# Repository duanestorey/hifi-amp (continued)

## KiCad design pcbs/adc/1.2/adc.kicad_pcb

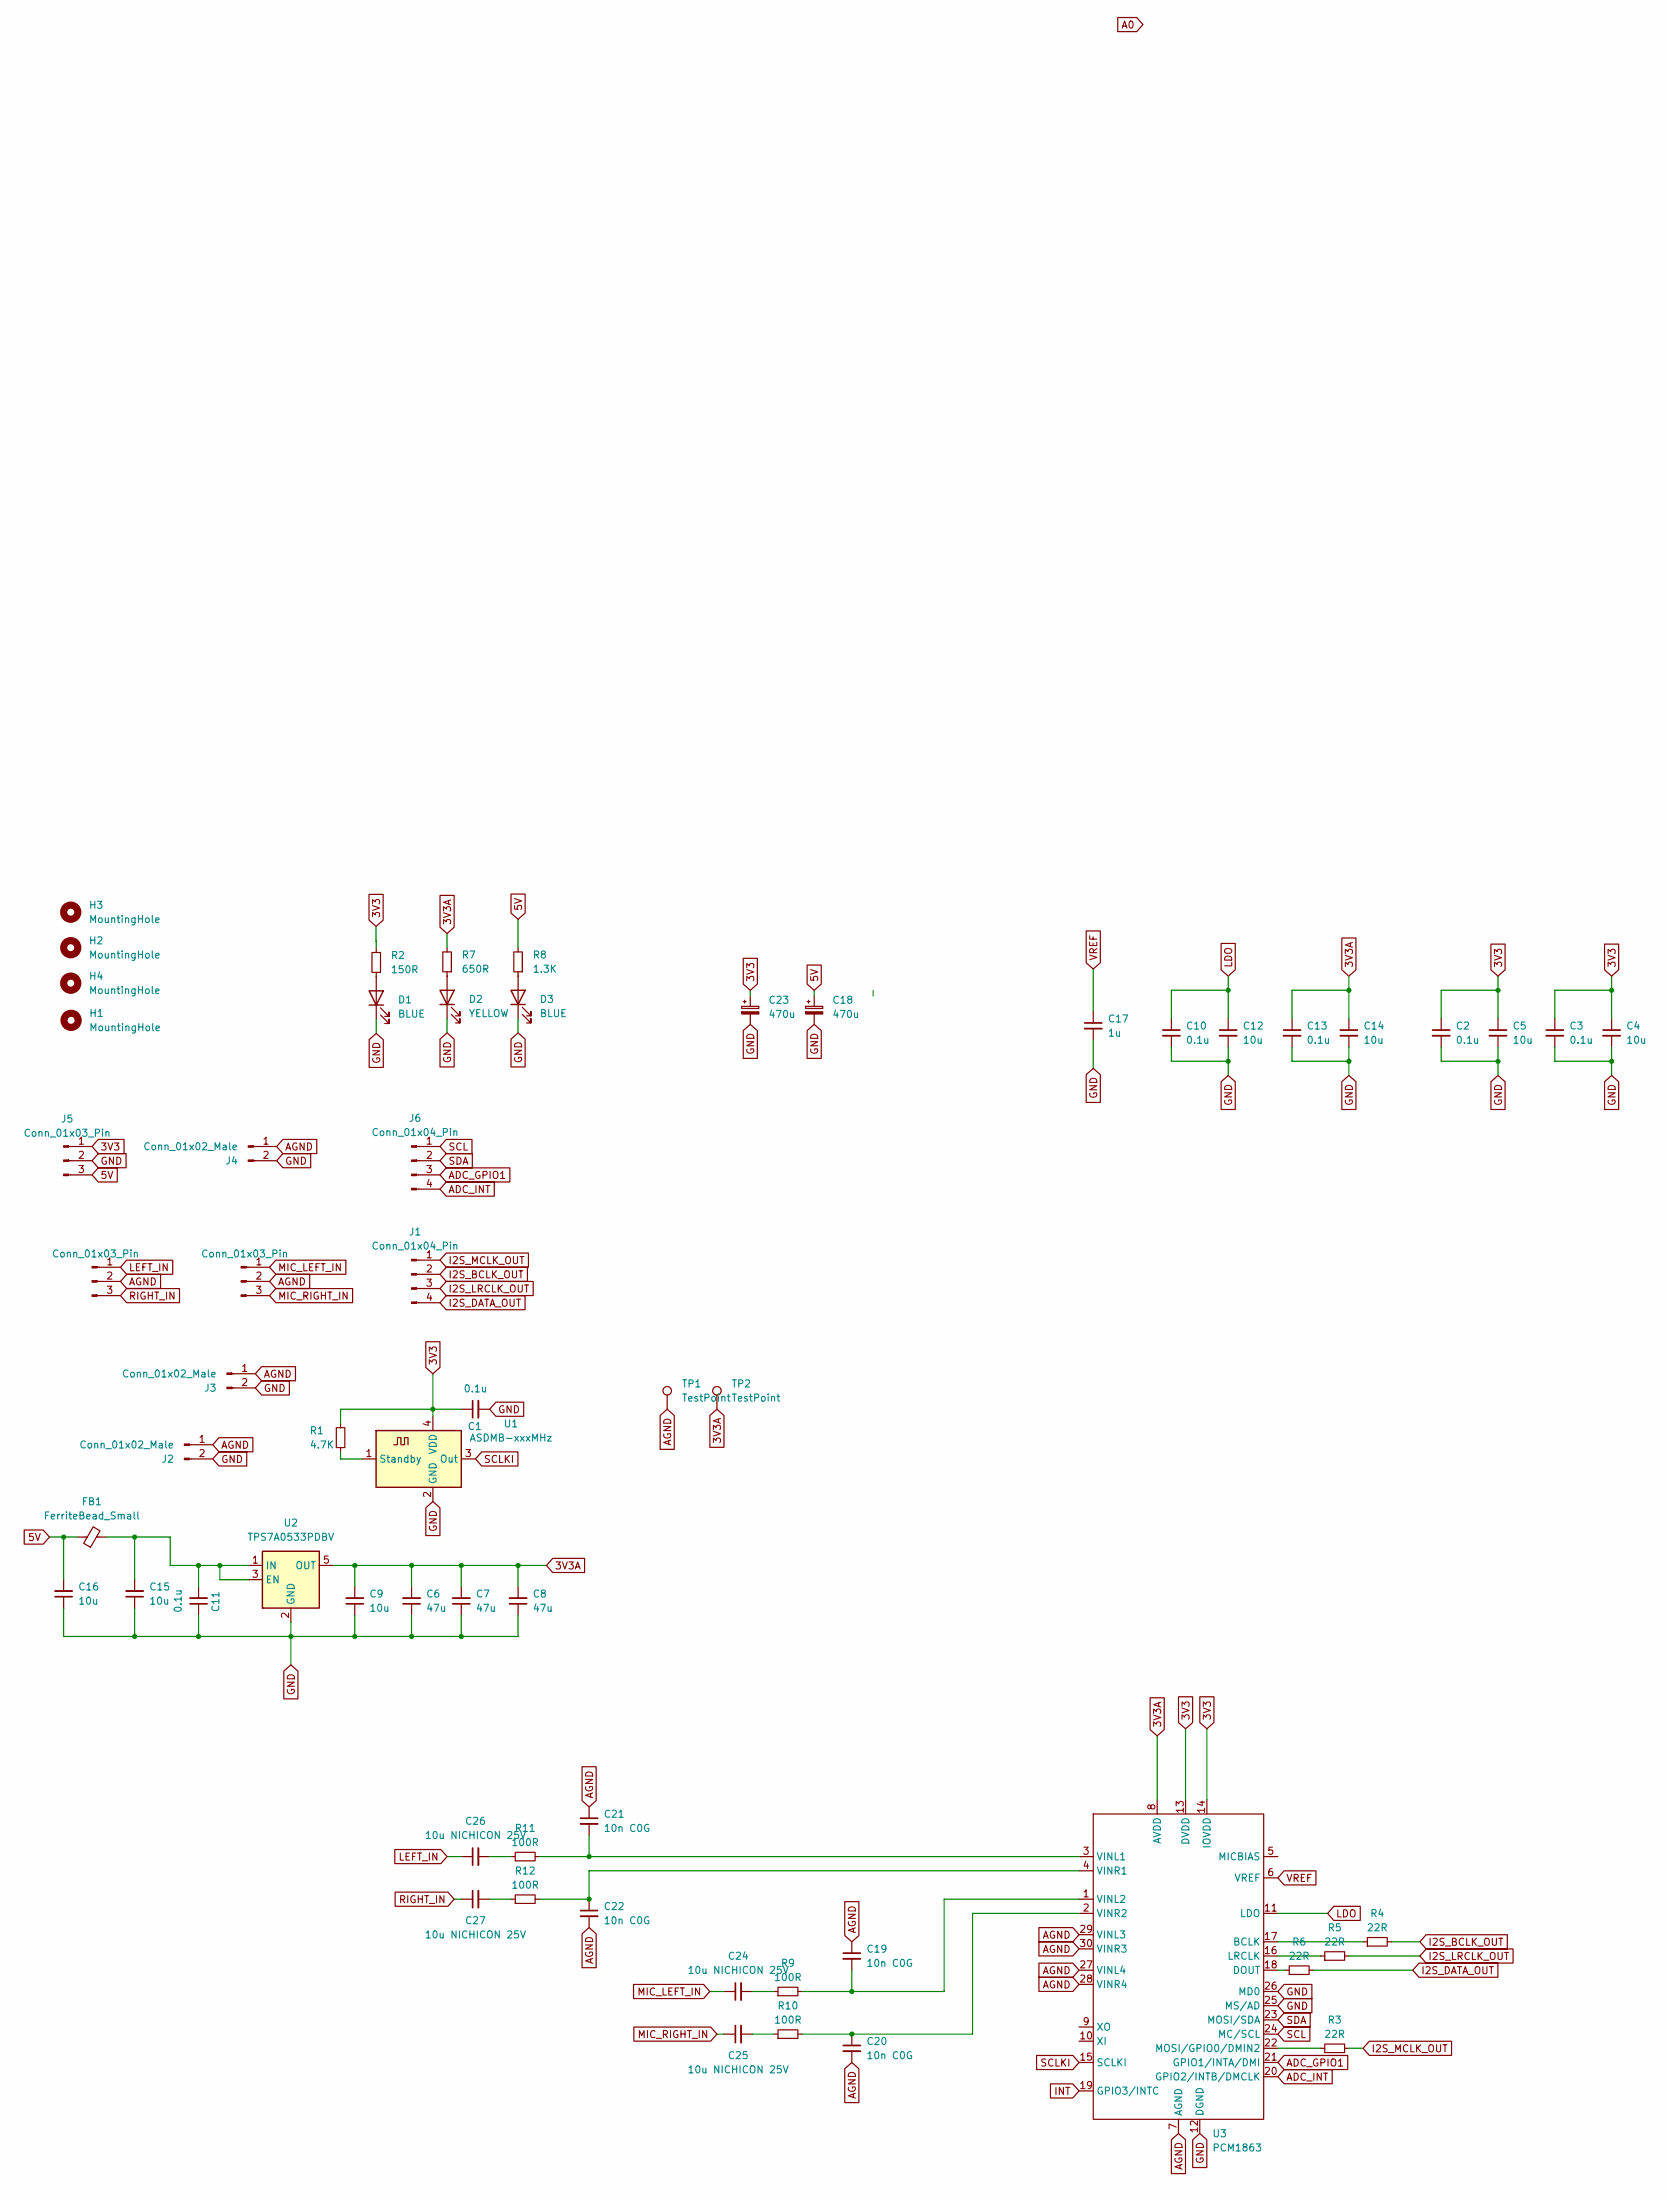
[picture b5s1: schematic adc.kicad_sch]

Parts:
C1, C11: 0.1u; C_0805_2012Metric_Pad1.18x1.45mm_HandSolder; Mouser 791-0805N103G250CT
C2, C3, C10, C13: 0.1u; C_0805_2012Metric_Pad1.18x1.45mm_HandSolder
C4, C5, C9, C12, C14, C15, C16: 10u; C_1206_3216Metric_Pad1.33x1.80mm_HandSolder
C6, C7, C8: 47u; C_1206_3216Metric_Pad1.33x1.80mm_HandSolder
C17: 1u; C_1206_3216Metric_Pad1.33x1.80mm_HandSolder
C18, C23: 470u; CP_Radial_D6.3mm_P2.50mm
C19, C20, C21, C22: 10n C0G; C_0805_2012Metric_Pad1.18x1.45mm_HandSolder; Mouser 791-0805N103G250CT
C24, C25, C26, C27: 10u NICHICON 25V; CP_Radial_D5.0mm_P2.00mm
D1, D3: BLUE; LED_0603_1608Metric
D2: YELLOW; LED_0603_1608Metric
FB1: FerriteBead_Small; R_0603_1608Metric_Pad0.98x0.95mm_HandSolder
H1, H2, H3, H4: MountingHole; MountingHole_3.2mm_M3_DIN965_Pad_TopOnly
J1, J6: Conn_01x04_Pin; JST_PH_B4B-PH-K_1x04_P2.00mm_Vertical
J2, J3, J4: Conn_01x02_Male; PinHeader_1x02_P2.54mm_Vertical
J5, J7, J8: Conn_01x03_Pin; JST_PH_B3B-PH-K_1x03_P2.00mm_Vertical
R1: 4.7K; R_0603_1608Metric_Pad0.98x0.95mm_HandSolder; Mouser 603-RT0805FRE0722RL
R2: 150R; R_0603_1608Metric_Pad0.98x0.95mm_HandSolder
R3, R4, R5, R6: 22R; R_0805_2012Metric_Pad1.20x1.40mm_HandSolder; Mouser 603-RT0805FRE0722RL
R7: 650R; R_0603_1608Metric_Pad0.98x0.95mm_HandSolder
R8: 1.3K; R_0603_1608Metric_Pad0.98x0.95mm_HandSolder
R9, R10, R11, R12: 100R; R_0805_2012Metric_Pad1.20x1.40mm_HandSolder; Mouser 603-RT0805FRE13100RL
TP1, TP2: TestPoint; TestPoint_THTPad_2.5x2.5mm_Drill1.2mm
U1: ASDMB-xxxMHz; Oscillator_SMD_Abracon_ASE-4Pin_3.2x2.5mm; Mouser 346-3225Z24.5760C1KX
U2: TPS7A0533PDBV; SOT-23-5
U3: PCM1863; TSSOP-30_4.4x7.8mm_P0.5mm; Mouser 595-PCM1863DBT

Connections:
3V3: C1.1, C2.1, C3.1, C4.1, C5.1, C23.1, J5.1, R1.1, R2.2, U1.4 (VDD), U3.13 (DVDD), U3.14 (IOVDD)
3V3A: C6.2, C7.2, C8.2, C9.2, C13.1, C14.1, R7.2, TP2.1, U2.5 (OUT), U3.8 (AVDD)
5V: C16.2, C18.1, FB1.1, J5.3, R8.2
ADC_GPIO1: J6.3, U3.21 (GPIO1/INTA/DMI)
ADC_INT: J6.4, U3.20 (GPIO2/INTB/DMCLK)
AGND: C19.1, C20.2, C21.1, C22.2, J2.1, J3.1, J4.1, J7.2, J8.2, TP1.1, U3.7 (AGND), U3.27 (VINL4), U3.28 (VINR4), U3.29 (VINL3), U3.30 (VINR3)
GND: C1.2, C2.2, C3.2, C4.2, C5.2, C6.1, C7.1, C8.1, C9.1, C10.2, C11.1, C12.2, C13.2, C14.2, C15.1, C16.1, C17.2, C18.2, C23.2, D1.1 (K), D2.1 (K), D3.1 (K), J2.2, J3.2, J4.2, J5.2, U1.2 (GND), U2.2 (GND), U3.12 (DGND), U3.25 (MS/AD), U3.26 (MD0)
I2S_BCLK_OUT: J1.2, R4.2
I2S_DATA_OUT: J1.4, R6.2
I2S_LRCLK_OUT: J1.3, R5.2
I2S_MCLK_OUT: J1.1, R3.2
INT: U3.19 (GPIO3/INTC)
LDO: C10.1, C12.1, U3.11 (LDO)
LEFT_IN: C26.1, J8.1
MIC_LEFT_IN: C24.1, J7.1
MIC_RIGHT_IN: C25.1, J7.3
unnamed: C24.2, R9.1
unnamed: C25.2, R10.1
unnamed: C26.2, R11.1
unnamed: C27.2, R12.1
unnamed: D1.2 (A), R2.1
unnamed: D2.2 (A), R7.1
unnamed: D3.2 (A), R8.1
unnamed: R1.2, U1.1 (Standby)
unnamed: C11.2, C15.2, FB1.2, U2.1 (IN), U2.3 (EN)
unnamed: R4.1, U3.17 (BCLK)
unnamed: R6.1, U3.18 (DOUT)
unnamed: R5.1, U3.16 (LRCLK)
unnamed: R3.1, U3.22 (MOSI/GPIO0/DMIN2)
unnamed: C21.2, R11.2, U3.3 (VINL1)
unnamed: C19.2, R9.2, U3.1 (VINL2)
unnamed: C22.1, R12.2, U3.4 (VINR1)
unnamed: C20.1, R10.2, U3.2 (VINR2)
RIGHT_IN: C27.1, J8.3
SCL: J6.1, U3.24 (MC/SCL)
SCLKI: U1.3 (Out), U3.15 (SCLKI)
SDA: J6.2, U3.23 (MOSI/SDA)
VREF: C17.1, U3.6 (VREF)

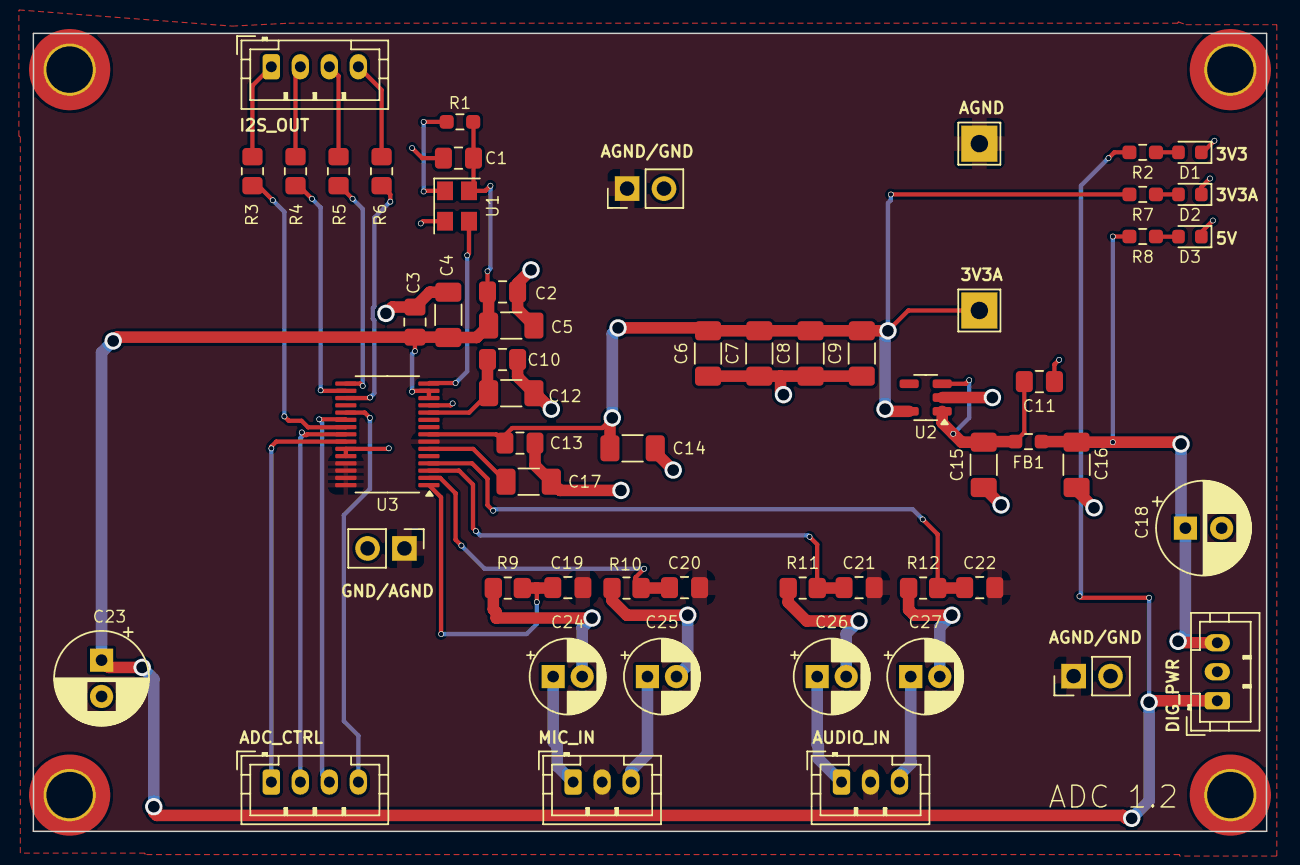
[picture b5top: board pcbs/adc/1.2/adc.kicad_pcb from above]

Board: 2 copper layers, 85.0 x 55.0 mm, 60 parts (0 on the bottom side), 37 nets.

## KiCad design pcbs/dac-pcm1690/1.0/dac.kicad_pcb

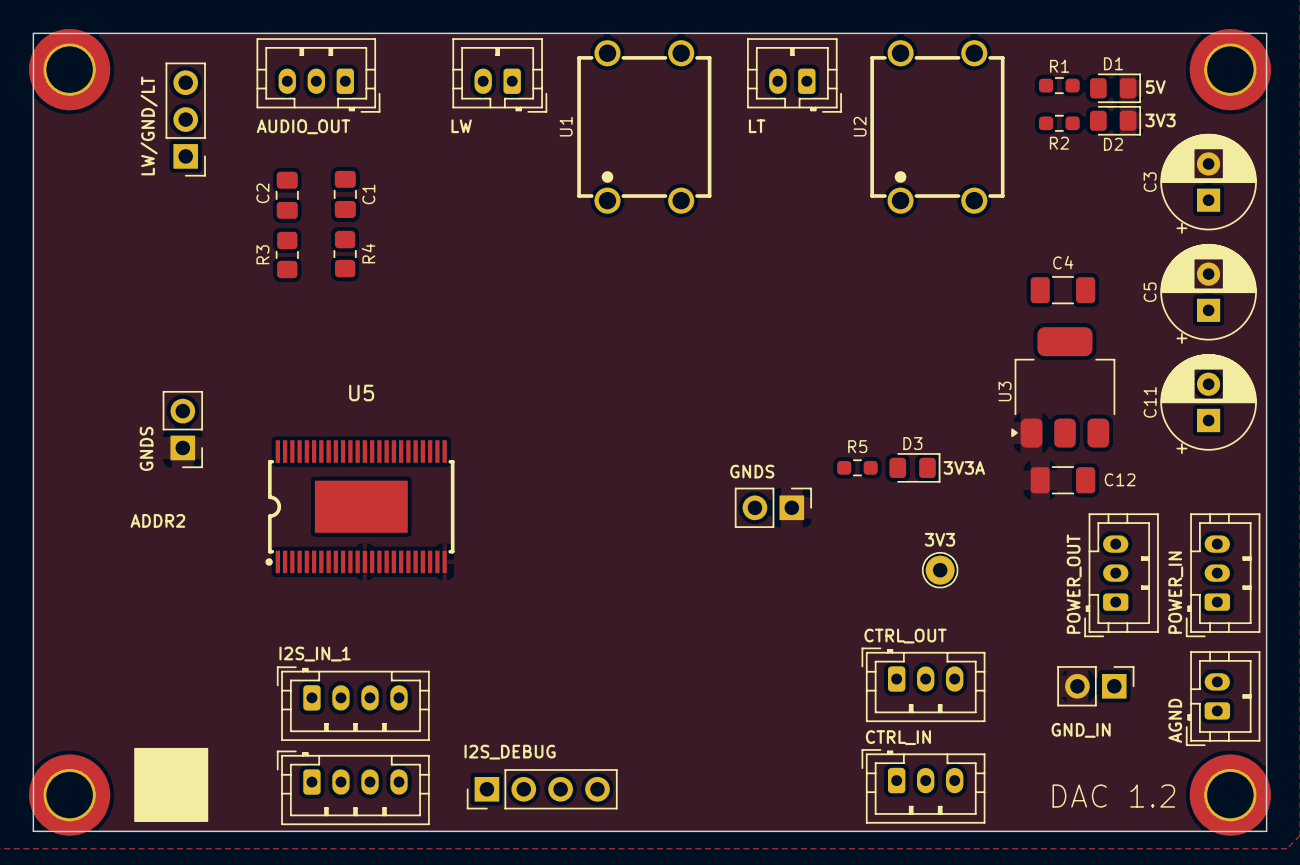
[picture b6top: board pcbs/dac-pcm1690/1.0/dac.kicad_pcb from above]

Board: 2 copper layers, 85.0 x 55.0 mm, 39 parts (0 on the bottom side), 22 nets, no tracks yet.

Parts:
C1, C2: 2.2n 50V C0G; C_0805_2012Metric_Pad1.18x1.45mm_HandSolder
C3, C5, C11: 220u; CP_Radial_D6.3mm_P2.50mm
C4, C12: 10U; C_1206_3216Metric_Pad1.33x1.80mm_HandSolder
D1: RED; LED_0805_2012Metric_Pad1.15x1.40mm_HandSolder
D2, D3: BLUE; LED_0805_2012Metric_Pad1.15x1.40mm_HandSolder
H1, H2, H3, H4: MountingHole; MountingHole_3.2mm_M3_DIN965_Pad_TopOnly
J1, J7, J13, J15, J16: Conn_01x03_Pin; JST_PH_B3B-PH-K_1x03_P2.00mm_Vertical
J2, J3, J18: Conn_01x02_Pin; JST_PH_B2B-PH-K_1x02_P2.00mm_Vertical
J4: Conn_01x03_Pin; PinHeader_1x03_P2.54mm_Vertical
J5, J10, J11: Conn_01x02_Pin; PinHeader_1x02_P2.54mm_Vertical
J12, J14: Conn_01x04_Pin; JST_PH_B4B-PH-K_1x04_P2.00mm_Vertical
J17: Conn_01x04_Pin; PinHeader_1x04_P2.54mm_Vertical
R1: 1.3K; R_0603_1608Metric_Pad0.98x0.95mm_HandSolder
R2, R5: 150R; R_0603_1608Metric_Pad0.98x0.95mm_HandSolder
R3, R4: 470R TF; R_0805_2012Metric_Pad1.20x1.40mm_HandSolder
TP4: TestPoint; TestPoint_THTPad_D2.0mm_Drill1.0mm
U1, U2: DA101C_C6931652; XFMR-TH_4P-L9.5-W9.0-P5.08-LS10.2_C9900096976
U3: ZLDO1117QG33TA; SOT-223-3_TabPin2
U5: PCM1690DCAR; HTSSOP-48_L12.5-W6.1-P0.50-LS8.1-BL-EP-1

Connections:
3V3: C3.1, J7.1, J13.1, R2.1, TP4.1, U5.12 (VDD)
3V3A: C4.1, C11.1, R5.1, U3.2 (VO)
5V: C5.1, C12.1, J7.3, J13.3, R1.1, U3.3 (VI), U5.25 (VCC1), U5.47 (VCC2)
AGND: C1.1, C2.1, C4.2, C11.2, D3.1 (K), J1.2, J4.2, J5.2, J10.2, J18.1, J18.2, U1.3, U2.3, U5.1 (RSV2), U5.3 (RSV2), U5.5 (RSV2), U5.27 (AGND1), U5.28 (RSV2), U5.46 (AGND2)
BCLK: J12.2, J14.2, J17.2
DATA: J12.4, J14.4, J17.4
GND: C3.2, C5.2, C12.2, D1.1 (K), D2.1 (K), J5.1, J10.1, J11.2, U3.1 (GND), U5.13 (DGND), U5.24 (MODE)
GND_IN: J7.2, J11.1, J13.2
LEFT_TWEETER: C2.2, J1.3, J4.3, R3.2, U2.1
LEFT_WOOFER: C1.2, J1.1, J4.1, R4.2, U1.1
LRCLK: J12.3, J14.3, J17.3
unnamed: D1.2 (A), R1.2
unnamed: D2.2 (A), R2.2
unnamed: D3.2 (A), R5.2
SCL: J15.1, J16.1
SCLK: J12.1, J14.1, J17.1
SDA: J15.2, J16.2
SWL_NEG: J2.1, U1.4
SWL_OUT: J2.2, U1.6
SWR_NEG: J3.1, U2.4
SWR_OUT: J3.2, U2.6
XSMT_IN: J15.3, J16.3

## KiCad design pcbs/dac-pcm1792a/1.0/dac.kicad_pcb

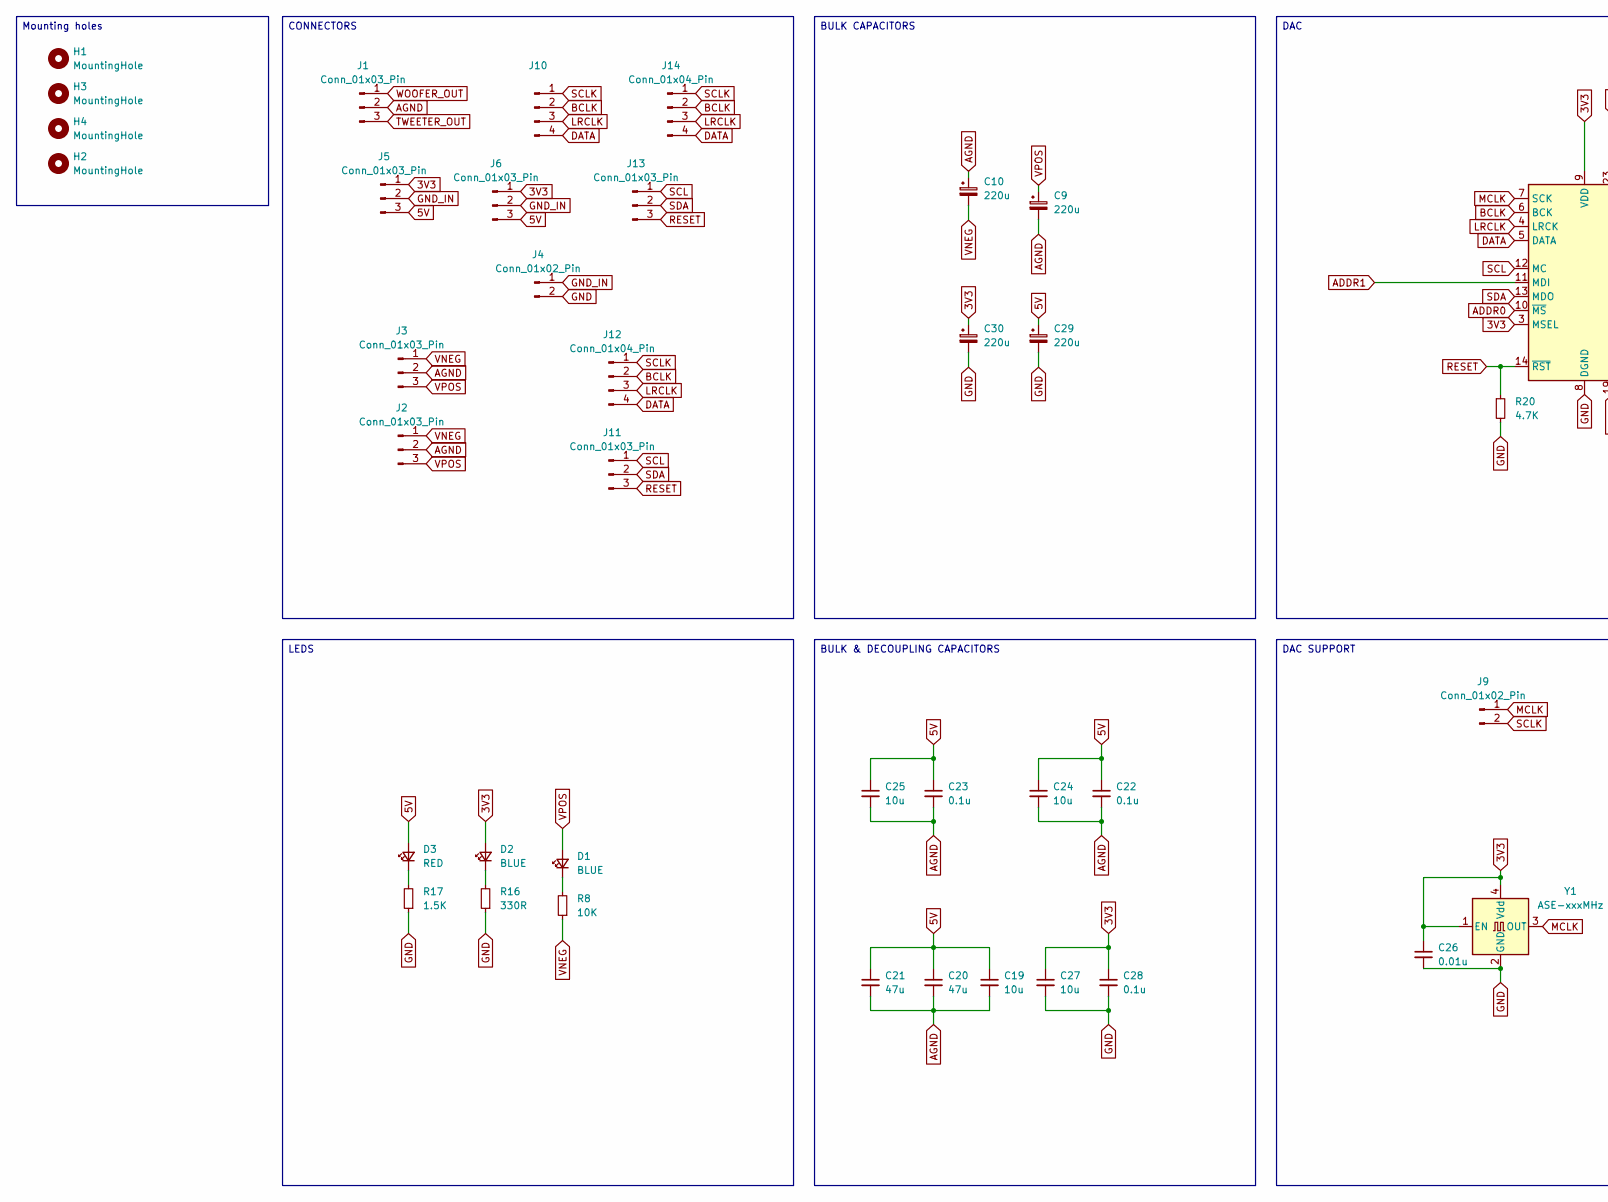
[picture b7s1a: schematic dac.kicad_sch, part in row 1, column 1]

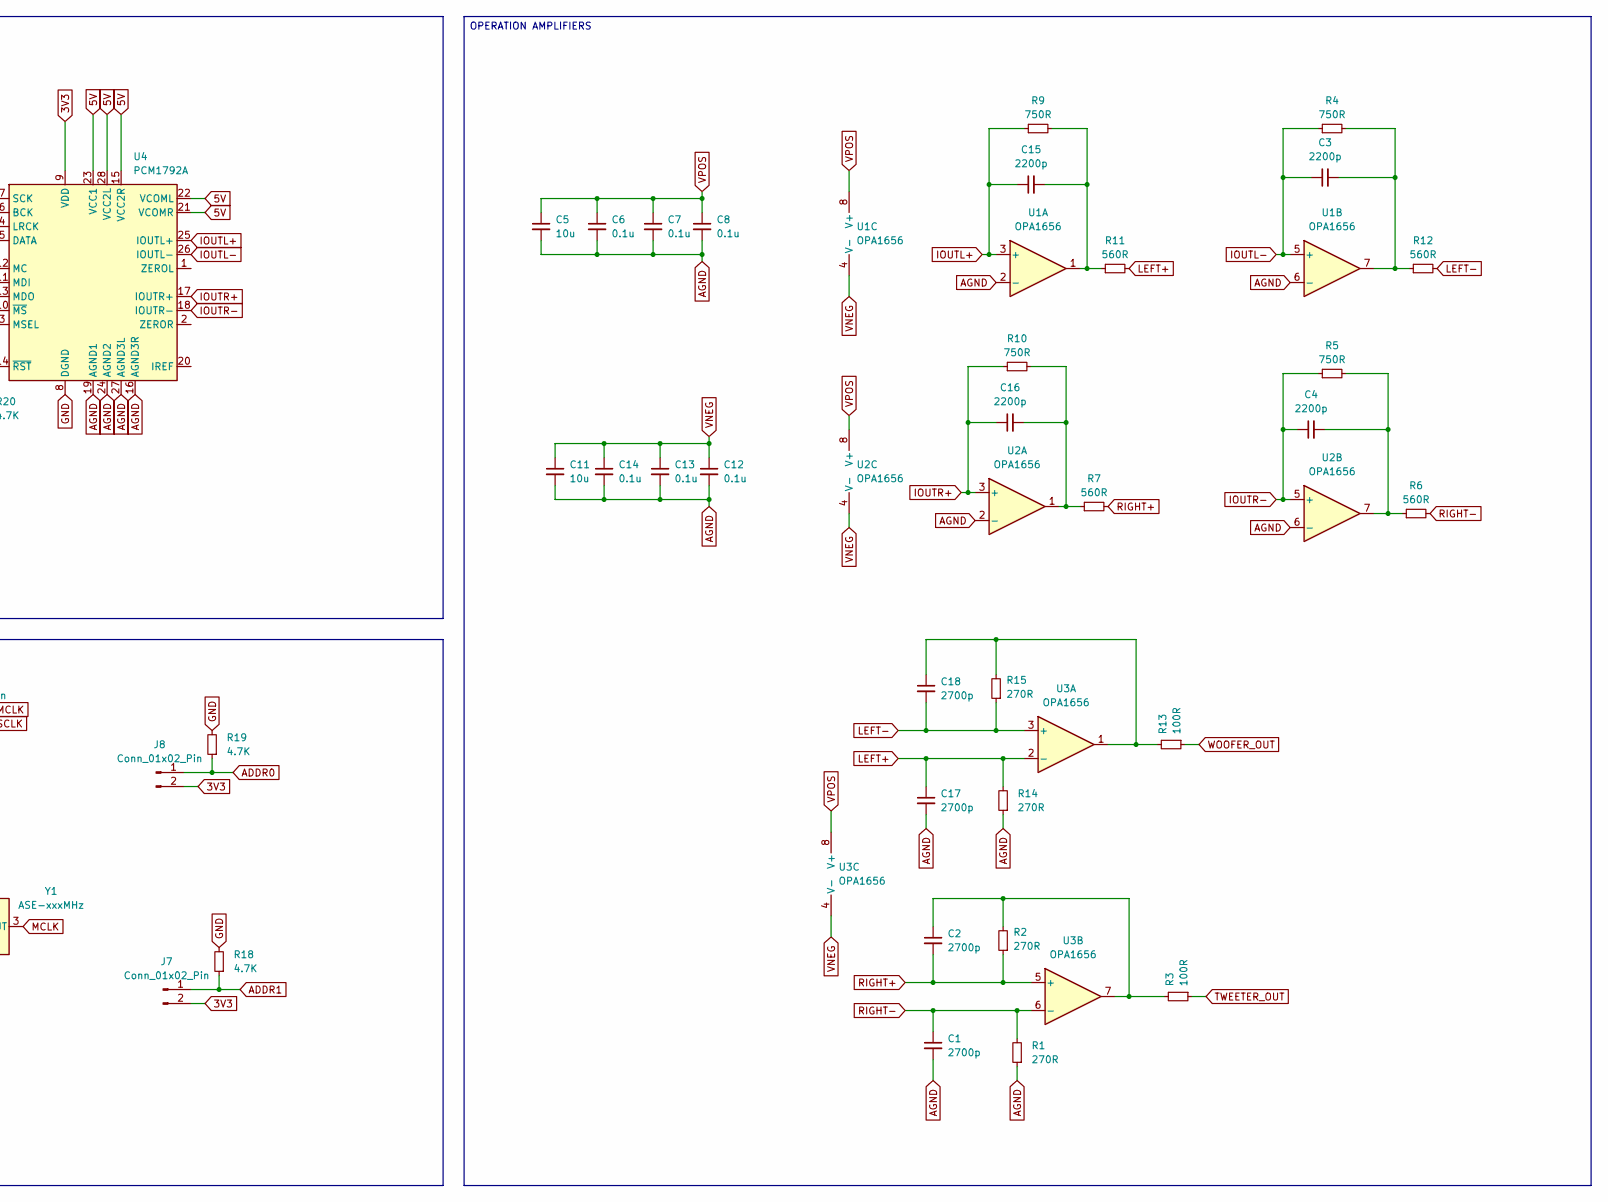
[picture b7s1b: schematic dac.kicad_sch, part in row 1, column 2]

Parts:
C1, C2, C17, C18: 2700p; C_0805_2012Metric_Pad1.18x1.45mm_HandSolder; Mouser CC0805FKNPO9BN272
C3, C4, C15, C16: 2200p; C_0805_2012Metric_Pad1.18x1.45mm_HandSolder; Mouser 0805N222G500CT
C5, C11, C19, C24, C25, C27: 10u; C_1206_3216Metric_Pad1.33x1.80mm_HandSolder
C6, C7, C8, C12, C13, C14, C22, C23, C28: 0.1u; C_0805_2012Metric_Pad1.18x1.45mm_HandSolder
C9, C10, C29, C30: 220u; CP_Radial_D6.3mm_P2.50mm
C20, C21: 47u; C_1206_3216Metric_Pad1.33x1.80mm_HandSolder
C26: 0.01u; C_0805_2012Metric_Pad1.18x1.45mm_HandSolder
D1, D2: BLUE; LED_0805_2012Metric_Pad1.15x1.40mm_HandSolder
D3: RED; LED_0805_2012Metric_Pad1.15x1.40mm_HandSolder
H1, H2, H3, H4: MountingHole; MountingHole_3.2mm_M3_DIN965_Pad_TopBottom
J1, J2, J3, J5, J6, J11, J13: Conn_01x03_Pin; JST_PH_B3B-PH-K_1x03_P2.00mm_Vertical
J4, J7, J8, J9: Conn_01x02_Pin; PinHeader_1x02_P2.54mm_Vertical
J10, J12: Conn_01x04_Pin; JST_PH_B4B-PH-K_1x04_P2.00mm_Vertical
J14: Conn_01x04_Pin; PinHeader_1x04_P2.54mm_Vertical
R1, R2, R14, R15: 270R; R_0805_2012Metric_Pad1.20x1.40mm_HandSolder; Mouser RT0805FRE07270RL
R3, R13: 100R; R_0805_2012Metric_Pad1.20x1.40mm_HandSolder; Mouser RT0805FRE13100RL
R4, R5, R9, R10: 750R; R_0805_2012Metric_Pad1.20x1.40mm_HandSolder; Mouser RT0805DRD07750RL
R6: 560R; R_0805_2012Metric_Pad1.20x1.40mm_HandSolder
R7, R11, R12: 560R; R_0805_2012Metric_Pad1.20x1.40mm_HandSolder; Mouser RT0805FRE07560RL
R8: 10K; R_0603_1608Metric_Pad0.98x0.95mm_HandSolder
R16: 330R; R_0603_1608Metric_Pad0.98x0.95mm_HandSolder
R17: 1.5K; R_0603_1608Metric_Pad0.98x0.95mm_HandSolder
R18, R19, R20: 4.7K; R_0603_1608Metric_Pad0.98x0.95mm_HandSolder
U1, U2, U3: OPA1656; DIP-8_W7.62mm
U4: PCM1792A; SSOP-28_5.3x10.2mm_P0.65mm; Mouser 595-PCM1792ADBR
Y1: ASE-xxxMHz; Oscillator_SMD_Abracon_ASE-4Pin_3.2x2.5mm_HandSoldering

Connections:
3V3: C26.1, C27.1, C28.1, C30.1, D2.2 (A), J5.1, J6.1, J7.2, J8.2, U4.3 (MSEL), U4.9 (VDD), Y1.1 (EN), Y1.4 (Vdd)
5V: C19.1, C20.1, C21.1, C22.1, C23.1, C24.1, C25.1, C29.1, D3.2 (A), J5.3, J6.3, U4.15 (VCC2R), U4.21 (VCOMR), U4.22 (VCOML), U4.23 (VCC1), U4.28 (VCC2L)
ADDR0: J8.1, R19.1, U4.10 (~MS)
ADDR1: J7.1, R18.1, U4.11 (MDI)
AGND: C1.2, C5.2, C6.2, C7.2, C8.2, C9.2, C10.1, C11.2, C12.2, C13.2, C14.2, C17.2, C19.2, C20.2, C21.2, C22.2, C23.2, C24.2, C25.2, J1.2, J2.2, J3.2, R1.1, R14.1, U1.2 (-), U1.6 (-), U2.2 (-), U2.6 (-), U4.16 (AGND3R), U4.19 (AGND1), U4.24 (AGND2), U4.27 (AGND3L)
BCLK: J10.2, J12.2, J14.2, U4.6 (BCK)
DATA: J10.4, J12.4, J14.4, U4.5 (DATA)
GND: C26.2, C27.2, C28.2, C29.2, C30.2, J4.2, R16.1, R17.1, R18.2, R19.2, R20.2, U4.8 (DGND), Y1.2 (GND)
GND_IN: J4.1, J5.2, J6.2
IOUTL+: C15.1, R9.1, U1.3 (+), U4.25 (IOUTL+)
IOUTL-: C3.1, R4.1, U1.5 (+), U4.26 (IOUTL-)
IOUTR+: C16.1, R10.1, U2.3 (+), U4.17 (IOUTR+)
IOUTR-: C4.1, R5.1, U2.5 (+), U4.18 (IOUTR-)
LEFT+: C17.1, R11.2, R14.2, U3.2 (-)
LEFT-: C18.2, R12.2, R15.1, U3.3 (+)
LRCLK: J10.3, J12.3, J14.3, U4.4 (LRCK)
MCLK: J9.1, U4.7 (SCK), Y1.3 (OUT)
unnamed: C2.1, R2.2, R3.2, U3.7
unnamed: C3.2, R4.2, R12.1, U1.7
unnamed: C4.2, R5.2, R6.1, U2.7
unnamed: C15.2, R9.2, R11.1, U1.1
unnamed: C16.2, R7.1, R10.2, U2.1
unnamed: C18.1, R13.2, R15.2, U3.1
unnamed: D1.1 (K), R8.2
unnamed: D2.1 (K), R16.2
unnamed: D3.1 (K), R17.2
RESET: J11.3, J13.3, R20.1, U4.14 (~RST)
RIGHT+: C2.2, R2.1, R7.2, U3.5 (+)
RIGHT-: C1.1, R1.2, R6.2, U3.6 (-)
SCL: J11.1, J13.1, U4.12 (MC)
SCLK: J9.2, J10.1, J12.1, J14.1
SDA: J11.2, J13.2, U4.13 (MDO)
TWEETER_OUT: J1.3, R3.1
VNEG: C10.2, C11.1, C12.1, C13.1, C14.1, J2.1, J3.1, R8.1, U1.4 (V-), U2.4 (V-), U3.4 (V-)
VPOS: C5.1, C6.1, C7.1, C8.1, C9.1, D1.2 (A), J2.3, J3.3, U1.8 (V+), U2.8 (V+), U3.8 (V+)
WOOFER_OUT: J1.1, R13.1

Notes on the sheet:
OPERATION AMPLIFIERS
CONNECTORS
DAC
DAC SUPPORT
BULK & DECOUPLING CAPACITORS
LEDS
BULK CAPACITORS
Mounting holes

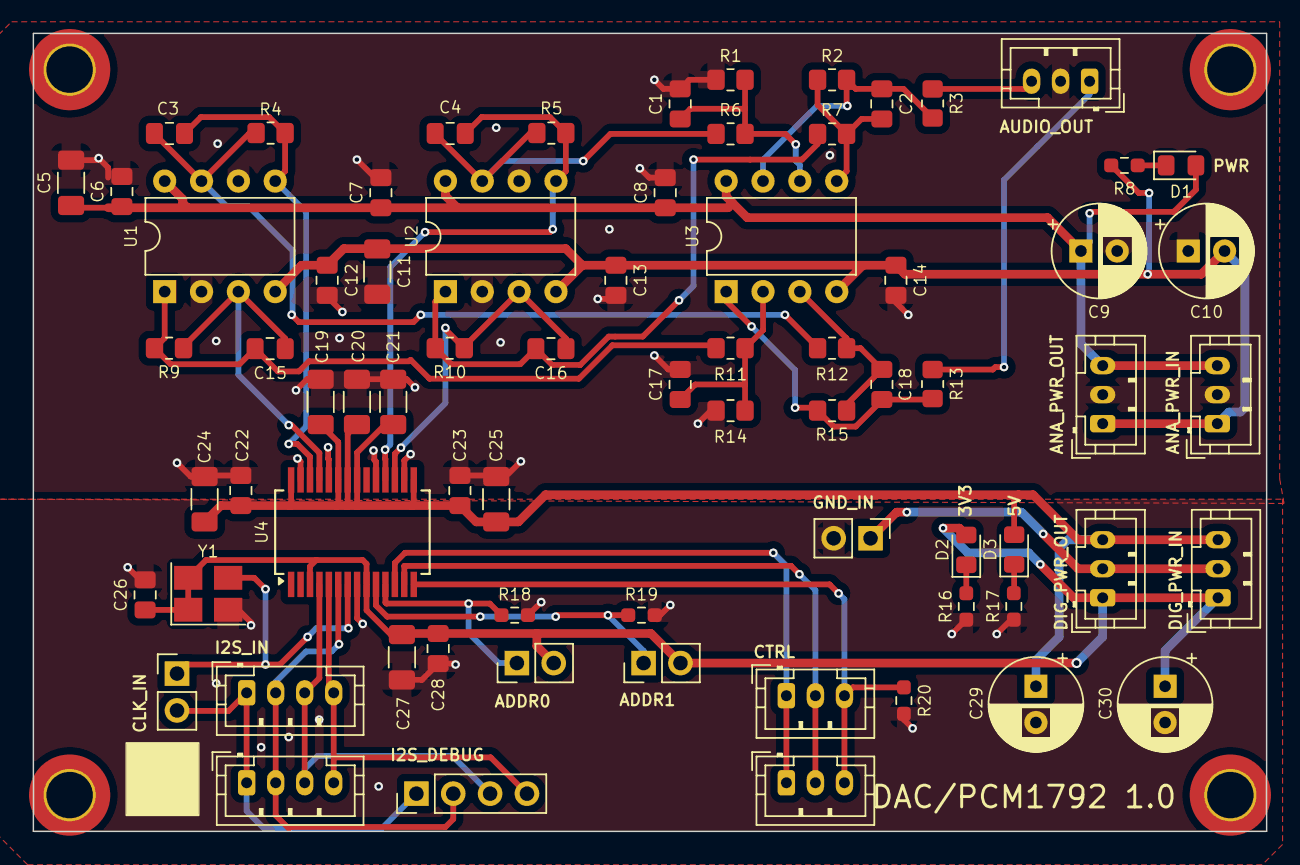
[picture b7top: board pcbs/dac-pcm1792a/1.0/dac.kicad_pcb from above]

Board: 4 copper layers, 85.0 x 55.0 mm, 76 parts (0 on the bottom side), 36 nets.

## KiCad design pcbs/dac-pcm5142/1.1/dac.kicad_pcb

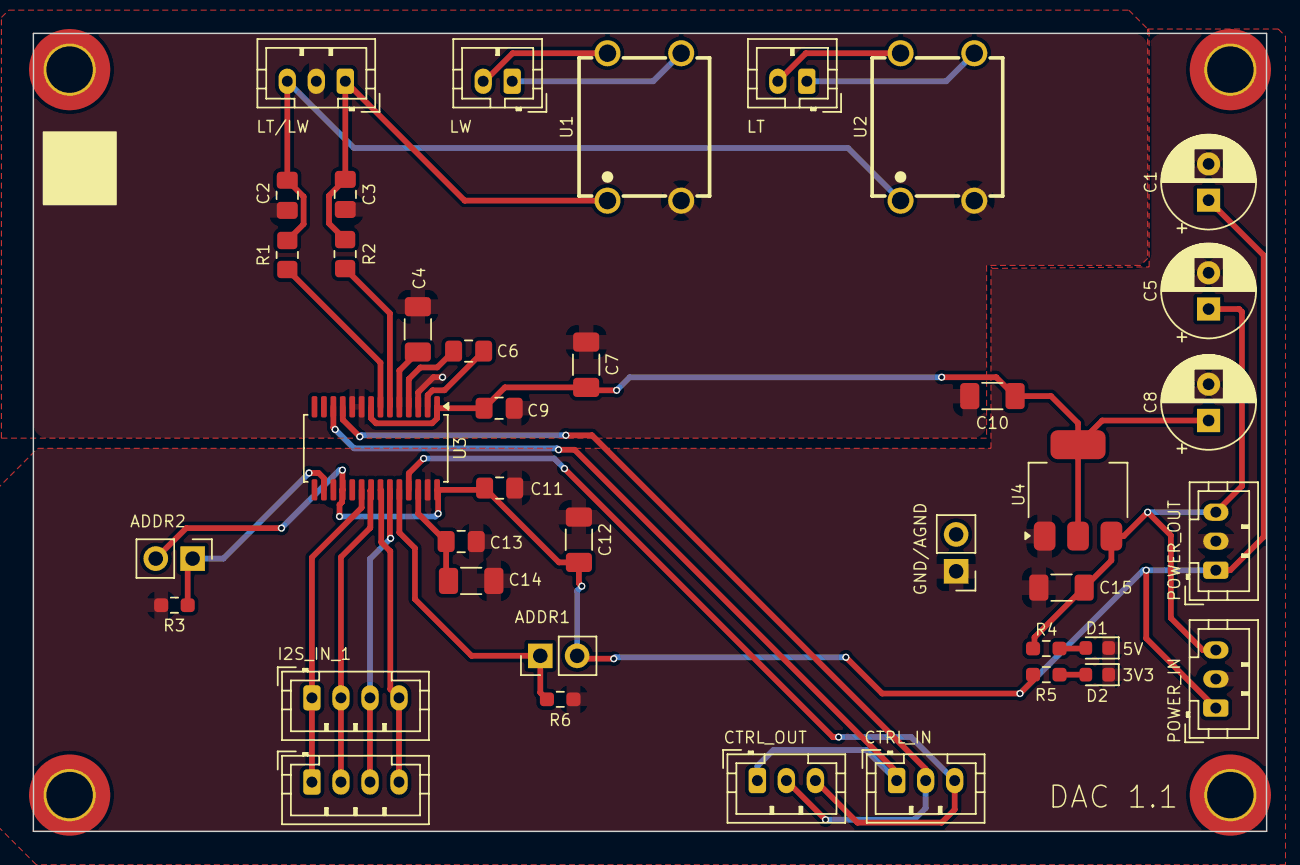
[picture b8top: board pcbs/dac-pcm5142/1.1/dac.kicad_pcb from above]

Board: 2 copper layers, 85.0 x 55.0 mm, 43 parts (0 on the bottom side), 28 nets.

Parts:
C1, C5, C8: 220u; CP_Radial_D6.3mm_P2.50mm
C2, C3: 2.2n 50V C0G; C_0805_2012Metric_Pad1.18x1.45mm_HandSolder
C4: 2.2u 25V; C_1206_3216Metric_Pad1.33x1.80mm_HandSolder
C6: 2.2u 25V; C_0805_2012Metric_Pad1.18x1.45mm_HandSolder
C7, C10, C12, C14, C15: 10U; C_1206_3216Metric_Pad1.33x1.80mm_HandSolder
C9, C11, C13: 0.1U; C_0805_2012Metric_Pad1.18x1.45mm_HandSolder
D1: RED; LED_0603_1608Metric
D2: BLUE; LED_0603_1608Metric
H1, H2, H3, H4: MountingHole; MountingHole_3.2mm_M3_DIN965_Pad_TopOnly
J1, J4, J9, J10, J11: Conn_01x03_Pin; JST_PH_B3B-PH-K_1x03_P2.00mm_Vertical
J2, J3: Conn_01x02_Pin; JST_PH_B2B-PH-K_1x02_P2.00mm_Vertical
J5, J6, J8: Conn_01x02_Pin; PinHeader_1x02_P2.54mm_Vertical
J7, J12: Conn_01x04_Pin; JST_PH_B4B-PH-K_1x04_P2.00mm_Vertical
R1, R2: 470R TF; R_0805_2012Metric_Pad1.20x1.40mm_HandSolder
R3, R6: 4.7K; R_0603_1608Metric_Pad0.98x0.95mm_HandSolder
R4: 1.3K; R_0603_1608Metric_Pad0.98x0.95mm_HandSolder
R5: 150R; R_0603_1608Metric_Pad0.98x0.95mm_HandSolder
U1, U2: DA101C_C6931652; XFMR-TH_4P-L9.5-W9.0-P5.08-LS10.2_C9900096976
U3: PCM5122PW; TSSOP-28_4.4x9.7mm_P0.65mm
U4: ZLDO1117QG33TA; SOT-223-3_TabPin2

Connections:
3V3: C1.1, C11.1, C12.1, J4.1, J5.2, J8.2, J9.1, R5.1, U3.18 (MODE2/MS), U3.28 (DVDD)
3V3A: C7.1, C8.1, C9.1, C10.1, U3.1 (CPVDD), U3.8 (AVDD), U4.2 (VO)
5V: C5.1, C15.1, J4.3, J9.3, R4.1, U4.3 (VI)
ADDR1: J8.1, R6.2, U3.24 (ADR1/MISO/FMT)
ADDR2: J5.1, R3.2, U3.16 (ADR2/GPIO2/DOUT)
AGND: C2.1, C3.1, C4.1, C7.2, C9.2, C10.2, J1.2, J6.2, U1.3, U2.3, U3.3 (CPGND), U3.9 (AGND), U3.10 (VCOM/DEMP)
BCLK0: J7.2, J12.2, U3.21 (BCK)
DATA0: J7.4, J12.4, U3.22 (DIN)
GND: C1.2, C5.2, C8.2, C11.2, C12.2, C13.1, C14.2, C15.2, D1.1 (K), D2.1 (K), J4.2, J6.1, J9.2, R3.1, R6.1, U3.17 (MODE1), U3.27 (DGND), U4.1 (GND)
LEFT_TWEETER: C2.2, J1.3, R1.2, U2.1
LEFT_WOOFER: C3.2, J1.1, R2.2, U1.1
LRCLK0: J7.3, J12.3, U3.23 (LRCK)
LT_OUT_PRE: R1.1, U3.7 (OUTR)
LW_OUT_PRE: R2.1, U3.6 (OUTL)
MCLK0: J7.1, J12.1, U3.20 (SCK)
unnamed: D1.2 (A), R4.2
unnamed: D2.2 (A), R5.2
unnamed: C6.2, U3.4 (CAPM)
unnamed: C6.1, U3.2 (CAPP)
unnamed: C13.2, C14.1, U3.26 (LDOO)
unnamed: C4.2, U3.5 (VNEG)
SCL: J10.1, J11.1, U3.12 (SCL/MC/ATT1)
SDA: J10.2, J11.2, U3.11 (SDA/MOSI/ATT2)
SWL_NEG: J2.1, U1.4
SWL_OUT: J2.2, U1.6
SWR_NEG: J3.1, U2.4
SWR_OUT: J3.2, U2.6
XSMT: J10.3, J11.3, U3.25 (XSMT)
